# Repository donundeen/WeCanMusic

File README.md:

# WeCanMusic

WeCanMusic is an open-source hardware and software platform that simplifies the creation of electronic musical instruments from simple found materials and the performance of these instruments by groups of people with no prior musical or performance experience. All sensor input is piped through a system that ensures that the notes produced follow chord changes that can be controlled in real time or composed in advance, allowing integration with live instruments and rock/pop bands. An WeCanMusic Jam Session brings participants together to explore the affordances of low-cost electronic sensors and consider how they can be combined with the materials on hand to create playful objects that generate sound when thrown, touched, bounced, shown colors, etc. These sensors, far from the techno-capitalist ideal of “perfect surveillance devices,” introduce their own noise, flutter and errors, which instead of being corrected, are drawn into dialogue with performers, influencing the aesthetics and acoustics of the performances. Entirely wireless, WeCanMusic performances can happen anywhere, with any number of people, or even with entirely non-human participants. In a new media art world that privileges technical virtuosity, WeCanMusic stubbornly asserts the importance of the amateur, the messy, the joyful. In short, WeCanMusic epowers an entirely different approach to music making, giving everyone a chance to join the jam.

# Included in this repo:

- arduino code to integrate a variety of sensors, on the Arduino Feather ESP32 platform
- Max/MSP patches to control the arduino devices according to a preset-score, and/or a web page allowing real-time chord changes
- NodeJs server which re-implements all Max/MSP features on open-source software, capable of running on a raspberry Pi
- NEW: new arduino code implements the Music Maker (midi synth) Featherwing, so note logic and midi tone production happens on the arduino itself, through attached speakers.
- NEW: Intergration with Pareto Anywhere, allowing the use of Off-the-shelf bluetooth devices as input devices, with audio output through virtual devices running on the server. 

Complete installation instructions coming shortly.

# Live Performances and Media:

- "Paleta De Aguacate, an WeCanMusic Performance", Morelia, Mexico:  https://www.youtube.com/watch?v=Ay2ICAsvL2w&t=2s&ab_channel=DonUndeen 

# In This Repo:

- **arduino**: Arduino files for running on Feather Huzzah ESP32 arduinos. 
  
  - **MaxCompatible**: arduino code for devices that just send thier raw values over UDP to a Max installation (in **PositionalJamAlphaBlast**). I've moved away from this approach to using the more open-source, RPi-based setup in **RPiCompatible**.
  
  - **RPiCompatible**: Arduino code for devices that take their sensor value, turn it into MIDI notes based on the supplied chord changes, and plays the notes using the attached MusicMaker featherwing. It ALSO can send the MIDI note as a makenote message over OSC/UDP, so that another computer could play it via an attached synth. This is useful if you don't have enough MusicMakers, or want to use fancier synths. There will be a sub-folder for each type of device, such as
    
    - **wecanmusic_capacitive**: The version of the device code for handling simple capacitive sensing, on pin 32.
      
      - Note, there are a bunch of files in here, but the only one that should change between types of devices is the one named the same as the folder. All other files should be the same between all devices.
  
  - **Utils:** Useful Utilities
    
    - **curveMaker.maxpat**: sometimes you want to finesse input values in arduino functions, so that an input value is mapped to an output with curve intead of a line, or even a series of curve segments. In this Max patch, you can draw the curve then dump a series of numbers that define the curve, then plug it into the arduino code. **TODO** Build a web interface for drawing curves, or at least selected from a set of pre-created curves.
    
    - **i2c_scanner.ino**:  When working with a bunch of different sensors, sometimes you need to see what i2c channels are in use. That's what this is for
    
    - **SPIFFS_mgmt:** The arduinos use SPIFFS for storing configuration values in non-volative memory. This arduino code helps manage that storage in case things get messy
  
  - **Tests**: Files I made to test things, and may want to refer to later.

- **server**: Files for running the Raspberry Pi server. If you don't need the Local WAP system, then you can run this server code on a Mac, but this setup isn't documented as well. See the README.md file in the **server** folder for installation and usage instructions.

- **VizStudioImplementation**: An implementation of this project that uses Max/MSP for most of the processing. In this setup, the devices simply send their raw values, and Max handles during those values into midi notes according to the chord changes, and sends MIDI values out. In this implmentation, the MIDI values are captured and played by Ableton; the ableton files are also in this folder. I've put aside this version in favor of the more open-source, wireless and headless version using the files in server and arduino folders instead. But there's lots of good stuff in here if you like working with Max.

## Hardware Used:

- Arduino Feather Case, with Battery Case: [Arduino Feather Cases](https://www.tinkercad.com/things/8DuQjJnMVJv-arduino-feather-cases) : this is only slightly modified from the case system created by Adafruit, which you can find here: [Adafruit Feather Box Enclosure by adafruit - Thingiverse](https://www.thingiverse.com/thing:2209964/files). The full assembly instructions and more options for configuration can be found here: [Overview | 3D Printed Case for Adafruit Feather | Adafruit Learning System](https://learn.adafruit.com/3d-printed-case-for-adafruit-feather/) 

- Adafruit HUZZAH32 ESP32 Feather Board: [Adafruit HUZZAH32 – ESP32 Feather ](https://www.adafruit.com/product/3405) 

- Adafruit Music Maker MP3 player and MIDI Synth: [Adafruit Music Maker](https://www.adafruit.com/product/3357) 

- Raspberry Pi 4 (but you can probably use other Pis)

- IQAudio DAC+: Provides much better audio quality than the built-in rpi audio outputs: https://www.pishop.ca/product/iqaudio-dac/ 

#

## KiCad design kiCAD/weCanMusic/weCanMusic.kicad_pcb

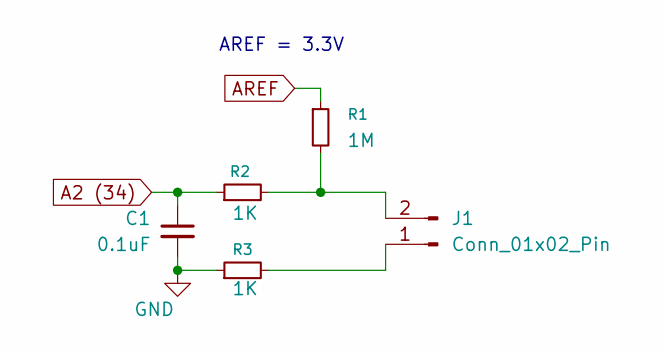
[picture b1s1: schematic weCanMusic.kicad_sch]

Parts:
C1: 0.1uF; C_0603_1608Metric
J1: Conn_01x02_Pin; PinHeader_1x02_P2.54mm_Vertical
R1: 1M; R_0603_1608Metric
R2, R3: 1K; R_0603_1608Metric

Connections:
A2 (34): C1.1, R2.1
AREF: R1.1
GND: C1.2, R3.1
unnamed: J1.1, R3.2
unnamed: J1.2, R1.2, R2.2

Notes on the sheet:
AREF = 3.3V

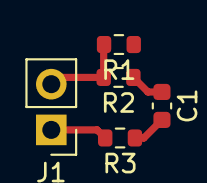
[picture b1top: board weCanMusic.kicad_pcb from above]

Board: 2 copper layers, 5 parts (0 on the bottom side), 4 nets.

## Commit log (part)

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2024-07-27 new notes
2024-07-29 new changes
2024-09-09 Create hotspotup.sh for bringing up hotspot
2024-10-07 volume control per voice. might have added breaking changes
2024-10-26 new integrations
2024-11-20 new code
2025-07-08 don's dinacon commit
